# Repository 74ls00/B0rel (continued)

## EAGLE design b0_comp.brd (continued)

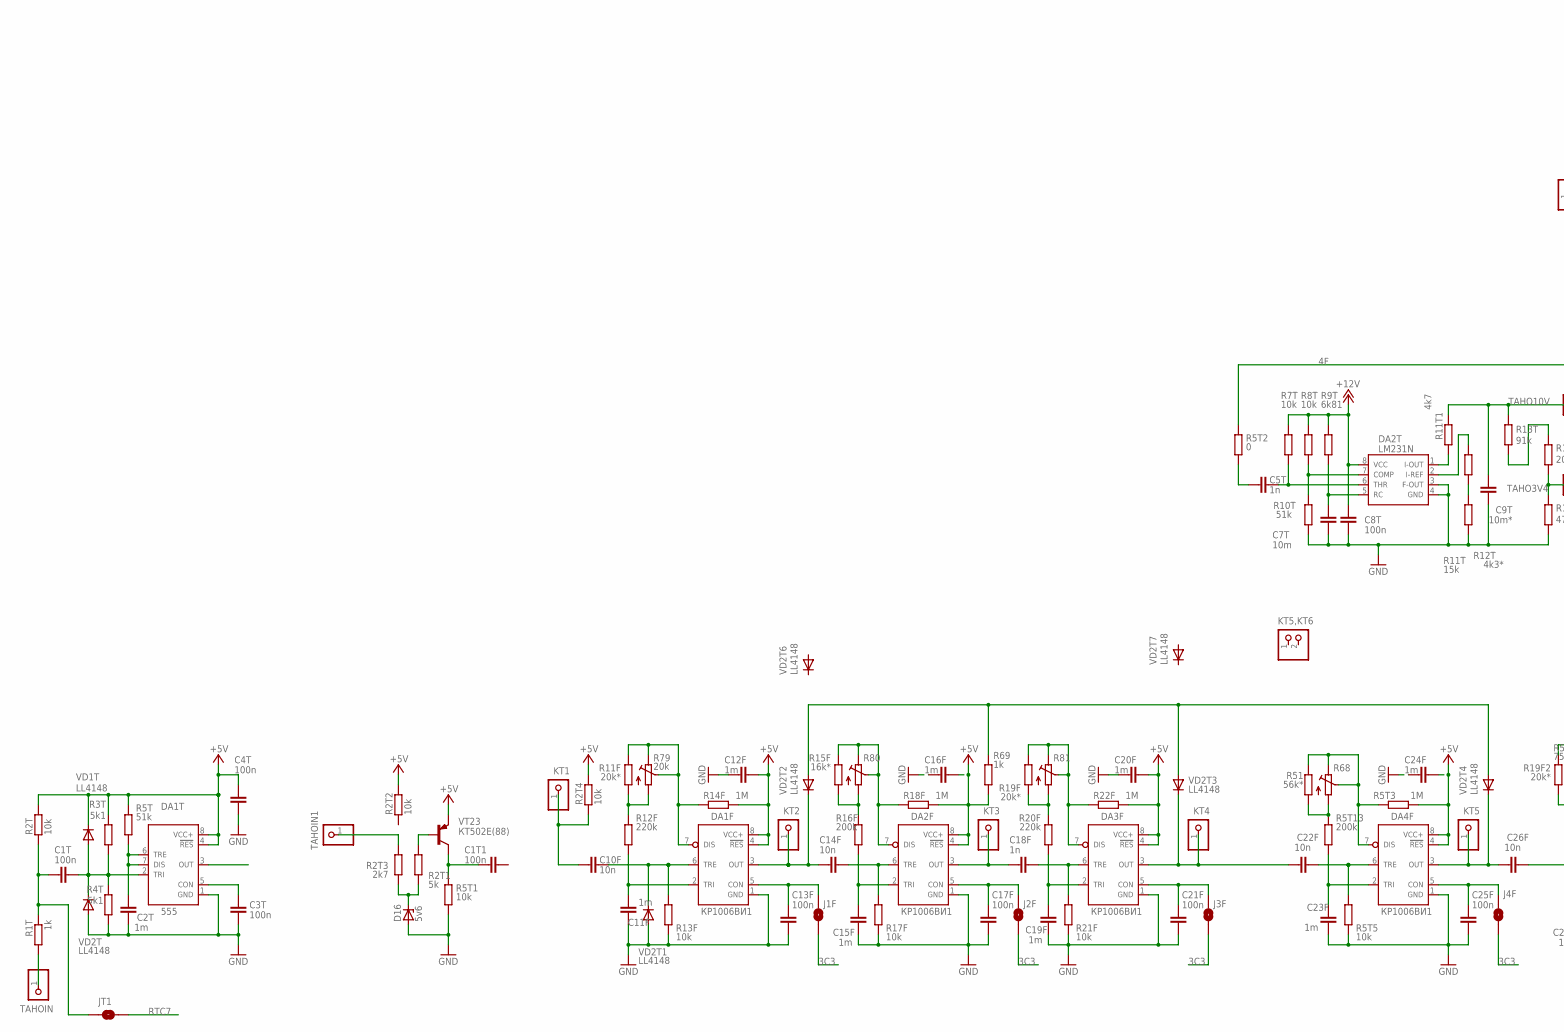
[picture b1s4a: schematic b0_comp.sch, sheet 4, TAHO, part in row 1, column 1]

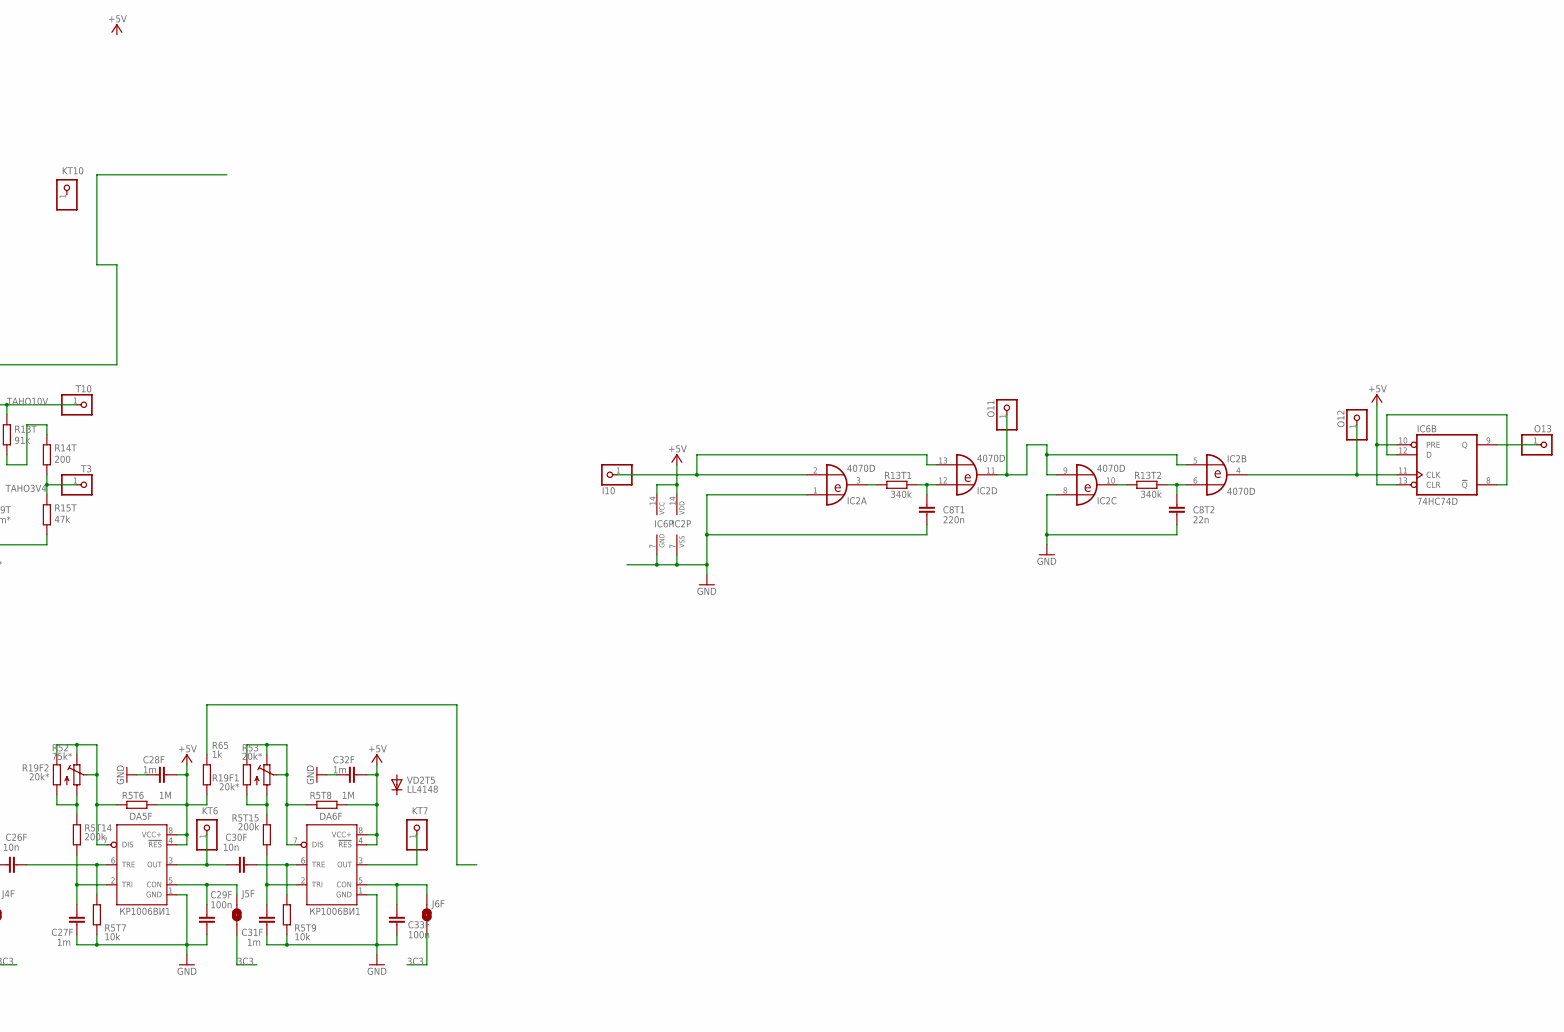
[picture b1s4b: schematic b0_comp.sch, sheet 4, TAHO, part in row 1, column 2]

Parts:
C1T, C1T1, C3T, C4T, C8T, C13F, C17F, C21F, C25F, C29F, C33F: 100n; C0805
C2T, C12F, C16F, C20F, C24F, C28F, C32F: 1m; C0805
C5T, C18F: 1n; C0805
C7T: 10m; C3225
C8T1: 220n; C0805
C8T2: 22n; C0805
C9T: 10m*; C3225
C10F, C14F, C22F, C26F, C30F: 10n; C0805
C11F, C15F, C19F, C23F, C27F, C31F: 1m; C90-065X115H
D16: 5v6; SOD80C
DA1F, DA2F, DA3F, DA4F, DA5F, DA6F: КР1006ВИ1; DIL8
DA1T: 555; DIL-08
DA2T: LM231N; DIL08
I10: PINHD-1X1; 1X01
IC2: 4070D; SO14
IC6: 74HC74D; SO14
J1F, J2F, J3F, J4F, J5F, J6F: SJ
JT1: SJ
KT1, KT2, KT3, KT4, KT5, KT6, KT7, KT10: PINHD-1X1; 1X01
KT5,KT6: PINHD-1X2/2; 1X02
O11, O12, O13: PINHD-1X1; 1X01
R1T, R65, R69: 1k; R0805
R2T, R2T2, R2T4, R5T1, R5T5, R5T7, R5T9, R7T, R8T, R13F, R17F, R21F: 10k; R0805
R2T1: 5k; R0805
R2T3: 2k7; R0805
R3T, R4T: 5k1; R0805
R5T, R10T: 51k; R0805
R5T2: 0; R0805
R5T3, R5T6, R5T8, R14F, R18F, R22F: 1M; R0805
R5T13, R5T14, R5T15, R16F: 200k; R0805
R9T: 6k81; R0805
R11F, R19F, R19F2: 20k*; 0207/10
R11T: 15k; R0805
R11T1: 4k7; R0805
R12F, R20F: 220k; R0805
R12T: 4k3*; R0805
R13T: 91k; R0805
R13T1, R13T2: 340k; R0805
R14T: 200; R0805
R15F: 16k*; 0207/10
R15T: 47k; R0805
R19F1: 20k*; 0207/11
R51: 56k*; 0207/10
R52: 75k*; RTRIM3314GJ
R53: 20k*; RTRIM3314G
R68, R80, R81: R-TRIMM3314GJ; RTRIM3314GJ
R79: 20k; RTRIM3314GJ
T3, T10: PINHD-1X1; 1X01
TAHOIN, TAHOIN1: PINHD-1X1; 1X01
VD1T, VD2T, VD2T1, VD2T2, VD2T3, VD2T4, VD2T5, VD2T6, VD2T7: LL4148; SOD80C
VT23: КТ502Е(88); TO92

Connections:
2F: R69.1, VD2T2.A, VD2T3.A, VD2T4.A
3C3: J1F.2, J2F.2, J3F.2, J4F.2, J5F.2, J6F.2
4F: R5T2.2
+5V: C4T.1, C12F.1, C16F.1, C20F.1, C24F.2, C28F.1, C32F.1, DA1F.4 (!RES), DA1F.8 (VCC+), DA1T.4 (!RES), DA1T.8 (VCC+), DA2F.4 (!RES), DA2F.8 (VCC+), DA3F.4 (!RES), DA3F.8 (VCC+), DA4F.4 (!RES), DA4F.8 (VCC+), DA5F.4 (!RES), DA5F.8 (VCC+), DA6F.4 (!RES), DA6F.8 (VCC+), IC2.14 (VDD), IC6.10 (PRE), IC6.13 (CLR), IC6.14 (VCC), R2T.2, R2T2.2, R2T4.2, R3T.2, R5T.2, R5T3.2, R5T6.2, R5T8.1, R14F.2, R18F.2, R22F.2, R65.2, R69.2, VD1T.C, VT23.3 (E); also elsewhere on the board
+12V: C8T.1, DA2T.8 (VCC), R7T.2, R8T.2, R9T.2; also elsewhere on the board
GND: C2T.2, C3T.2, C4T.2, C7T.2, C8T.2, C8T1.2, C8T2.2, C9T.2, C11F.1, C12F.2, C13F.2, C15F.2, C16F.2, C17F.2, C19F.2, C20F.2, C21F.2, C23F.2, C24F.1, C25F.2, C27F.2, C28F.2, C29F.2, C31F.2, C32F.2, C33F.2, D16.A, DA1F.1 (GND), DA1T.1 (GND), DA2F.1 (GND), DA2T.3 (F-OUT), DA2T.4 (GND), DA3F.1 (GND), DA4F.1 (GND), DA5F.1 (GND), DA6F.1 (GND), IC2.1 (I0), IC2.7 (VSS), IC2.8 (I0), IC6.7 (GND), R4T.1, R5T1.1, R5T5.1, R5T7.1, R5T9.1, R10T.1, R12T.1, R13F.1, R15T.1, R17F.1, R21F.1, VD2T.A, VD2T1.A; also elsewhere on the board
unnamed: C1T.1, JT1.1, R1T.1, R2T.1
unnamed: C25F.1, DA4F.5 (CON), J4F.1
unnamed: C3T.1, DA1T.5 (CON)
unnamed: D16.C, R2T1.1, R2T3.2
unnamed: C2T.1, DA1T.6 (TRE), DA1T.7 (DIS), R5T.1
unnamed: C23F.1, DA4F.2 (TRI), R5T13.1
unnamed: C1T1.1, R5T1.2, VT23.1 (C)
unnamed: R2T1.2, VT23.2 (B)
unnamed: R2T3.1, TAHOIN1.1
unnamed: C11F.2, DA1F.2 (TRI), R12F.1
unnamed: R1T.2, TAHOIN.1
unnamed: C1T.2, DA1T.2 (TRI), R3T.1, R4T.2, VD1T.A, VD2T.C
unnamed: I10.1, IC2.2 (I1), IC2.13 (I1)
unnamed: C7T.1, DA2T.5 (RC), R9T.1
unnamed: DA2T.7 (COMP), R8T.1, R10T.2
unnamed: DA2T.2 (I-REF), R11T.2
unnamed: R13T.2, R14T.2
unnamed: C5T.2, DA2T.6 (THR), R7T.1
unnamed: DA1F.7 (DIS), R11F.2, R14F.1, R79.1 (E), R79.1A (E), R79.2 (S)
unnamed: C10F.2, DA1F.6 (TRE), R13F.2, VD2T1.C
unnamed: C17F.1, DA2F.5 (CON), J2F.1
unnamed: R11F.1, R12F.2, R79.3 (A), R79.3A (A)
unnamed: C15F.1, DA2F.2 (TRI), R16F.1
unnamed: R11T.1, R12T.2
unnamed: DA2F.7 (DIS), R15F.2, R18F.1, R80.1 (E), R80.1A (E), R80.2 (S)
unnamed: C13F.1, DA1F.5 (CON), J1F.1
unnamed: C21F.1, DA3F.5 (CON), J3F.1
unnamed: R15F.1, R16F.2, R80.3 (A), R80.3A (A)
unnamed: C19F.1, DA3F.2 (TRI), R20F.1
unnamed: DA3F.7 (DIS), R19F.2, R22F.1, R81.1 (E), R81.1A (E), R81.2 (S)
unnamed: C18F.2, DA3F.6 (TRE), R21F.2
unnamed: C14F.2, DA2F.6 (TRE), R17F.2
unnamed: R19F.1, R20F.2, R81.3 (A), R81.3A (A)
unnamed: C5T.1, R5T2.1
unnamed: C10F.1, KT1.1, R2T4.1
unnamed: C22F.1, DA3F.3 (OUT), KT4.1, VD2T3.C
unnamed: C18F.1, DA2F.3 (OUT), KT3.1
unnamed: C29F.1, DA5F.5 (CON), J5F.1
unnamed: C14F.1, DA1F.3 (OUT), KT2.1, VD2T2.C
unnamed: C33F.1, DA6F.5 (CON), J6F.1
unnamed: DA6F.3 (OUT), KT7.1
unnamed: IC2.4 (O), IC6.11 (CLK), O12.1
unnamed: IC2.3 (O), R13T1.2
unnamed: C8T1.1, IC2.12 (I0), R13T1.1
unnamed: IC6.8 (!Q), IC6.12 (D)
unnamed: IC2.10 (O), R13T2.2
unnamed: DA2T.1 (I-OUT), R11T1.1
unnamed: IC2.5 (I0), IC2.9 (I1), IC2.11 (O), O11.1
unnamed: C8T2.1, IC2.6 (I1), R13T2.1
unnamed: R5T13.2, R51.1, R68.3 (A), R68.3A (A)
unnamed: R5T14.2, R19F2.1, R52.3 (A), R52.3A (A)
unnamed: IC6.9 (Q), O13.1
unnamed: DA4F.7 (DIS), R5T3.1, R51.2, R68.1 (E), R68.1A (E), R68.2 (S)
unnamed: C26F.1, DA4F.3 (OUT), KT5.1, VD2T4.C
unnamed: R5T15.2, R19F1.1, R53.3 (A)
unnamed: C22F.2, DA4F.6 (TRE), R5T5.2
unnamed: C27F.1, DA5F.2 (TRI), R5T14.1
unnamed: DA5F.7 (DIS), R5T6.1, R19F2.2, R52.1 (E), R52.1A (E), R52.2 (S)
unnamed: C26F.2, DA5F.6 (TRE), R5T7.2
unnamed: C31F.1, DA6F.2 (TRI), R5T15.1
unnamed: DA6F.7 (DIS), R5T8.2, R19F1.2, R53.1 (E), R53.2 (S)
unnamed: C30F.2, DA6F.6 (TRE), R5T9.2
unnamed: C30F.1, DA5F.3 (OUT), KT6.1
RTC7: JT1.2; also elsewhere on the board
TAHO3V4: R14T.1, R15T.2, T3.1
TAHO10V: C9T.1, R11T1.2, R13T.1, T10.1

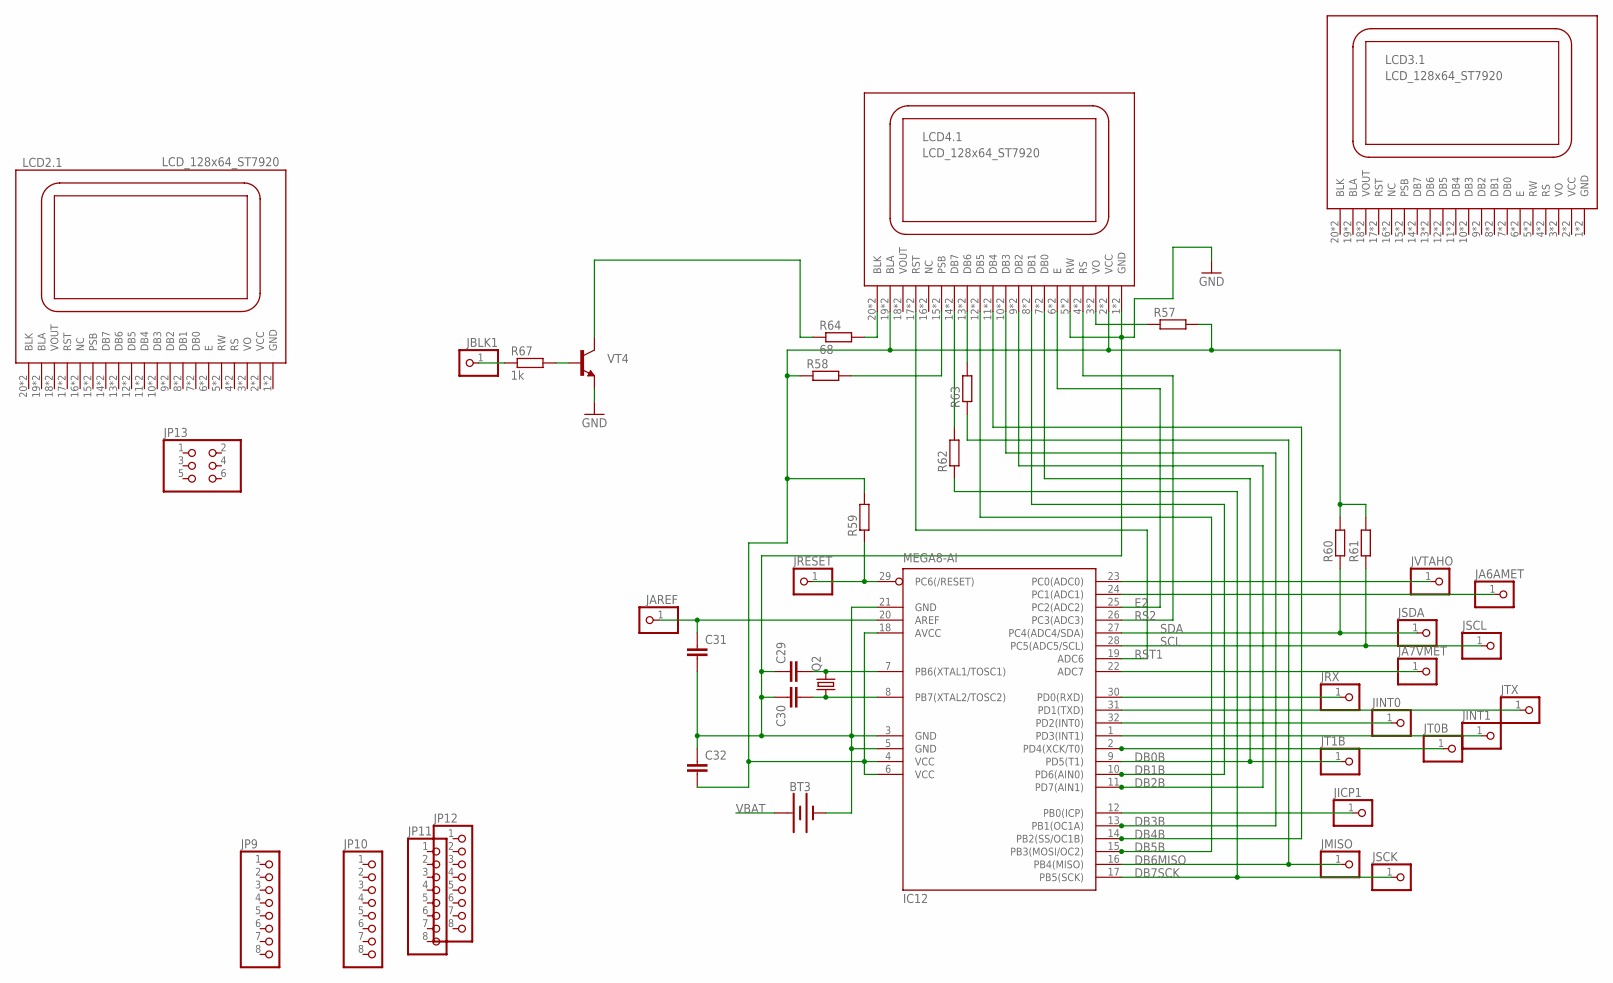
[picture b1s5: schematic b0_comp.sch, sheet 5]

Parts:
BT3: BATTERY-20MM_PTH; BATTCOM_20MM_PTH
C29, C30, C31, C32: C-EUC0805; C0805
IC12: MEGA8-AI; TQFP32-08
JA6AMET, JA7VMET: PINHD-1X1; 1X01
JAREF: PINHD-1X1; 1X01
JBLK1: PINHD-1X1; 1X01
JICP1: PINHD-1X1; 1X01
JINT0, JINT1: PINHD-1X1; 1X01
JMISO: PINHD-1X1; 1X01
JP9, JP10, JP11, JP12: PINHD-1X8; 1X08
JP13: PINHD-2X3/90; 2X03/90
JRESET: PINHD-1X1; 1X01
JRX: PINHD-1X1; 1X01
JSCK: PINHD-1X1; 1X01
JSCL: PINHD-1X1; 1X01
JSDA: PINHD-1X1; 1X01
JT0B, JT1B: PINHD-1X1; 1X01
JTX: PINHD-1X1; 1X01
JVTAHO: PINHD-1X1; 1X01
LCD2, LCD3, LCD4: LCD_128x64_ST7920; 12864B
Q2: CRYSTALHC49S; HC49/S
R57, R58, R59, R60, R61: R-EU_R0805; R0805
R62, R63: R-EU_R0603; R0603
R64: 68; R0805
R67: 1k; R0805
VT4: BJT_NPN_SOT23_BCE; SOT23

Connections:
DB0B: IC12.9 (PD5(T1)), JT1B.1, LCD4.7 (DB0), LCD4.7@ (DB0)
DB1B: IC12.10 (PD6(AIN0)), LCD4.8 (DB1), LCD4.8@ (DB1)
DB2B: IC12.11 (PD7(AIN1)), LCD4.9 (DB2), LCD4.9@ (DB2)
DB3B: IC12.13 (PB1(OC1A)), LCD4.10 (DB3), LCD4.10@ (DB3)
DB4B: IC12.14 (PB2(SS/OC1B)), LCD4.11 (DB4), LCD4.11@ (DB4)
DB5B: IC12.15 (PB3(MOSI/OC2)), LCD4.12 (DB5), LCD4.12@ (DB5)
DB6MISO: IC12.16 (PB4(MISO)), JMISO.1, R63.1
DB7SCK: IC12.17 (PB5(SCK)), JSCK.1, R62.1
E2: IC12.25 (PC2(ADC2)), LCD4.6 (E), LCD4.6@ (E)
GND: BT3.2 (-), C29.1, C30.1, C31.2, C32.1, IC12.3 (GND), IC12.5 (GND), IC12.21 (GND), LCD4.1 (GND), LCD4.1@ (GND), LCD4.5 (RW), LCD4.5@ (RW), VT4.2 (E); also elsewhere on the board
unnamed: R67.2, VT4.1 (B)
unnamed: R64.1, VT4.3 (C)
unnamed: JBLK1.1, R67.1
unnamed: LCD4.3 (VO), LCD4.3@ (VO), R57.1
unnamed: IC12.32 (PD2(INT0)), JINT0.1
unnamed: IC12.12 (PB0(ICP)), JICP1.1
unnamed: LCD4.15 (PSB), LCD4.15@ (PSB), R58.2
unnamed: IC12.2 (PD4(XCK/T0)), JT0B.1
unnamed: IC12.30 (PD0(RXD)), JRX.1
unnamed: IC12.22 (ADC7), JA7VMET.1
unnamed: IC12.24 (PC1(ADC1)), JA6AMET.1
unnamed: IC12.29 (PC6(/RESET)), JRESET.1, R59.1
unnamed: IC12.23 (PC0(ADC0)), JVTAHO.1
unnamed: LCD4.14 (DB7), LCD4.14@ (DB7), R62.2
unnamed: C29.2, IC12.7 (PB6(XTAL1/TOSC1)), Q2.2
unnamed: C30.2, IC12.8 (PB7(XTAL2/TOSC2)), Q2.1
unnamed: LCD4.13 (DB6), LCD4.13@ (DB6), R63.2
unnamed: IC12.1 (PD3(INT1)), JINT1.1
unnamed: LCD4.20 (BLK), LCD4.20@ (BLK), R64.2
unnamed: IC12.31 (PD1(TXD)), JTX.1
unnamed: C31.1, IC12.20 (AREF), JAREF.1
RS2: IC12.26 (PC3(ADC3)), LCD4.4 (RS), LCD4.4@ (RS)
RST1: IC12.19 (ADC6), LCD4.17 (RST), LCD4.17@ (RST)
SCL: IC12.28 (PC5(ADC5/SCL)), JSCL.1, R61.1; also elsewhere on the board
SDA: IC12.27 (PC4(ADC4/SDA)), JSDA.1, R60.1; also elsewhere on the board
VBAT: BT3.1 (+); also elsewhere on the board
VCCV2: C32.2, IC12.4 (VCC), IC12.6 (VCC), IC12.18 (AVCC), LCD4.2 (VCC), LCD4.2@ (VCC), LCD4.19 (BLA), LCD4.19@ (BLA), R57.2, R58.1, R59.2, R60.2, R61.2

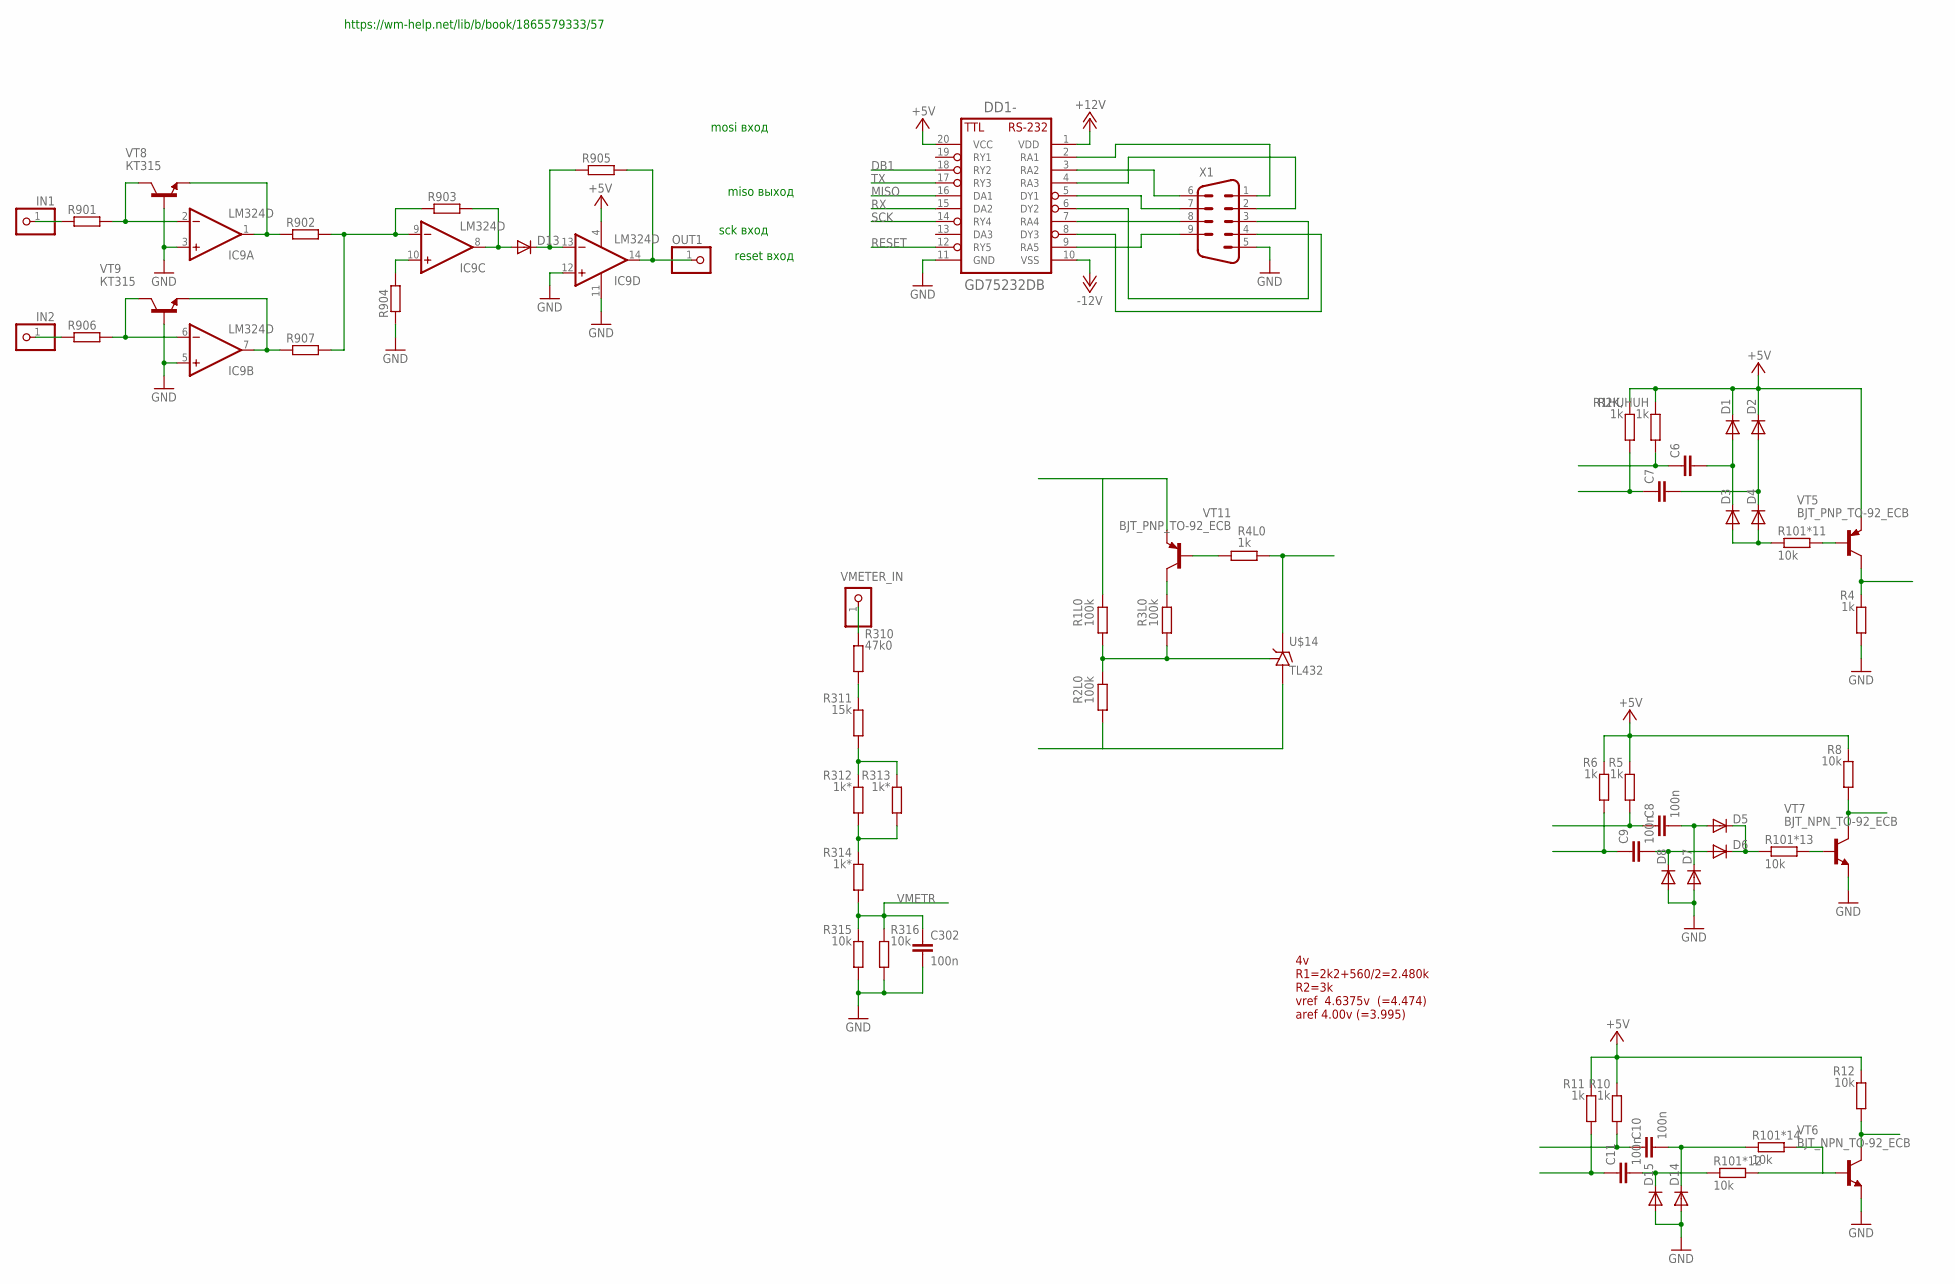
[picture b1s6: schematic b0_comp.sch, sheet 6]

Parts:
C6, C7: C-EUC0805; C0805
C8, C9, C10, C11, C302: 100n; C0805
D1, D2, D3, D4, D5, D6, D7, D8, D13, D14, D15: DIODE-SOD80C; SOD80C
DD1-: GD75232DB; SSOP20D8
IC9: LM324D; SO14
IN1, IN2: PINHD-1X1; 1X01
OUT1: PINHD-1X1; 1X01
R1HUHUH, R2K,, R4, R4L0, R5, R6, R10, R11: 1k; R0805
R1L0, R2L0, R3L0: 100k; R0805
R8, R12, R101*11, R101*12, R101*13, R101*14, R315, R316: 10k; R0805
R310: 47k0; R0805
R311: 15k; R0805
R312, R313, R314: 1k*; R0805
R901, R902, R903, R904, R905, R906, R907: R-EU_R0805; R0805
U$14: TL432; SOT-23
VMETER_IN: PINHD-1X1; 1X01
VT5, VT11: BJT_PNP_TO-92_ECB; TO92
VT6, VT7: BJT_NPN_TO-92_ECB; TO92
VT8, VT9: КТ315; TO92
X1: M09-182; 182-009-MALE

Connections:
+5V: D1.C, D2.C, DD1-.20 (VCC), IC9.4 (V+), R1HUHUH.2, R2K,.2, R5.2, R6.2, R8.2, R10.2, R11.2, R12.2, VT5.1 (E); also elsewhere on the board
+12V: DD1-.1 (VDD); also elsewhere on the board
-12V: DD1-.10 (VSS)
DB1: DD1-.18 (RY2); also elsewhere on the board
GND: C302.2, D7.A, D8.A, D14.A, D15.A, DD1-.11 (GND), IC9.3 (+IN), IC9.5 (+IN), IC9.11 (V-), IC9.12 (+IN), R4.1, R315.1, R316.1, R904.1, VT6.1 (E), VT7.1 (E), VT8.3 (B), VT9.3 (B), X1.5; also elsewhere on the board
MISO: DD1-.16 (DA1); also elsewhere on the board
unnamed: R312.1, R313.1, R314.2
unnamed: D3.A, D4.A, R101*11.1
unnamed: C6.2, D1.A, D3.C
unnamed: C7.2, D2.A, D4.C
unnamed: R101*13.2, VT7.3 (B)
unnamed: R101*11.2, VT5.3 (B)
unnamed: C6.1, R1HUHUH.1
unnamed: C7.1, R2K,.1
unnamed: C8.2, D5.A, D7.C
unnamed: R4.2, VT5.2 (C)
unnamed: C9.2, D6.A, D8.C
unnamed: C8.1, R5.1
unnamed: C9.1, R6.1
unnamed: R8.1, VT7.2 (C)
unnamed: D5.C, D6.C, R101*13.1
unnamed: C10.1, R10.1
unnamed: C11.1, R11.1
unnamed: C10.2, D14.C, R101*14.1
unnamed: R101*12.2, R101*14.2, VT6.3 (B)
unnamed: DD1-.9 (RA5), X1.9
unnamed: R12.1, VT6.2 (C)
unnamed: C11.2, D15.C, R101*12.1
unnamed: DD1-.8 (DY3), X1.4
unnamed: DD1-.7 (RA4), X1.8
unnamed: R310.1, R311.2
unnamed: DD1-.6 (DY2), X1.3
unnamed: DD1-.5 (DY1), X1.7
unnamed: DD1-.4 (RA3), X1.2
unnamed: DD1-.3 (RA2), X1.6
unnamed: DD1-.2 (RA1), X1.1
unnamed: R311.1, R312.2, R313.2
unnamed: R310.2, VMETER_IN.1
unnamed: IC9.6 (-IN), R906.2, VT9.2 (C)
unnamed: R3L0.2, VT11.2 (C)
unnamed: R4L0.1, VT11.3 (B)
unnamed: R4L0.2, U$14.2 (C)
unnamed: R1L0.2, VT11.1 (E)
unnamed: R2L0.1, U$14.3 (A)
unnamed: R1L0.1, R2L0.2, R3L0.1, U$14.1 (R)
unnamed: IC9.2 (-IN), R901.2, VT8.2 (C)
unnamed: IC9.1 (OUT), R902.1, VT8.1 (E)
unnamed: IC9.7 (OUT), R907.1, VT9.1 (E)
unnamed: IC9.9 (-IN), R902.2, R903.1, R907.2
unnamed: IC9.10 (+IN), R904.2
unnamed: D13.A, IC9.8 (OUT), R903.2
unnamed: D13.C, IC9.13 (-IN), R905.1
unnamed: IC9.14 (OUT), OUT1.1, R905.2
unnamed: IN1.1, R901.1
unnamed: IN2.1, R906.1
RESET: DD1-.12 (RY5); also elsewhere on the board
RX: DD1-.15 (DA2)
SCK: DD1-.14 (RY4); also elsewhere on the board
TX: DD1-.17 (RY3)
VMETR: C302.1, R314.1, R315.2, R316.2; also elsewhere on the board

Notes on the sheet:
https://wm-help.net/lib/b/book/1865579333/57
mosi вход
sck вход
miso выход
reset вход
4v R1=2k2+560/2=2.480k R2=3k vref 4.6375v (=4.474) aref 4.00v (=3.995)

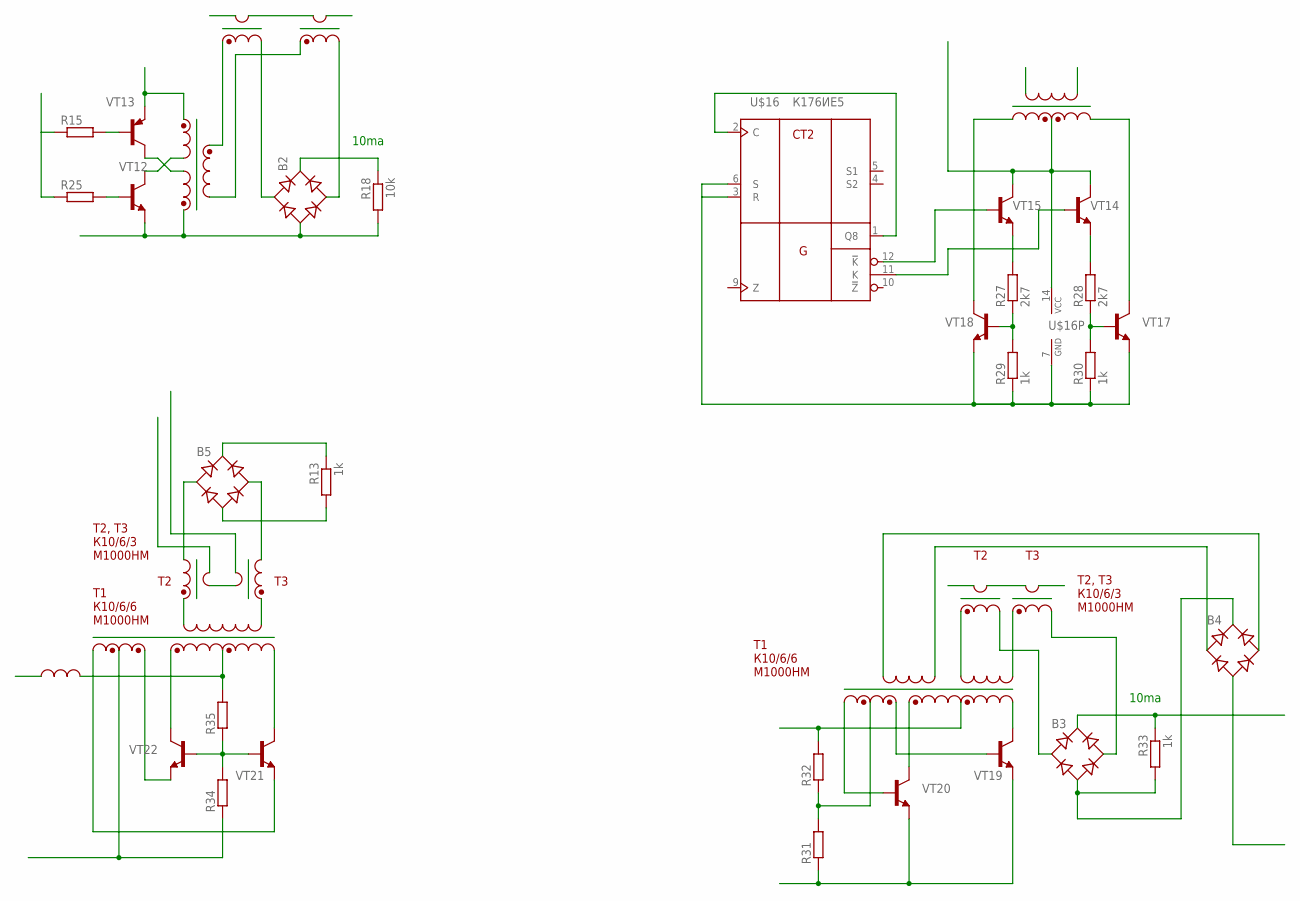
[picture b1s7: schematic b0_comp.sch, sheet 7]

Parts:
B2, B3, B4, B5: DBDB105G; DB
R13, R33: 1k; 0411/12
R15, R25, R31, R32, R34, R35: R-EU_0411/12; 0411/12
R18: 10k; 0411/12
R27, R28: 2k7; R0805
R29, R30: 1k; R0805
U$16: К176ИЕ5; DIL14
VT12, VT19, VT20, VT21, VT22: BJT_NPN_TO-92_CBE; TO92
VT13: BJT_PNP_SOT23_BCE; SOT23
VT14, VT15, VT17, VT18: BJT_NPN_TO-92_ECB; TO92

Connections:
unnamed: B5.-, R13.2
unnamed: B5.+, R13.1
unnamed: R15.2, VT13.1 (B)
unnamed: B2.-, R18.2, VT12.3 (E)
unnamed: B2.+, R18.1
unnamed: R25.2, VT12.2 (B)
unnamed: R15.1, R25.1
unnamed: U$16.1 (Q8), U$16.2 (C)
unnamed: U$16.12 (!K), VT15.3 (B)
unnamed: U$16.11 (K), VT14.3 (B)
unnamed: U$16.14 (VCC), VT14.2 (C), VT15.2 (C)
unnamed: R28.1, R30.2, VT17.3 (B)
unnamed: R28.2, VT14.1 (E)
unnamed: R27.2, VT15.1 (E)
unnamed: R27.1, R29.2, VT18.3 (B)
unnamed: R29.1, R30.1, U$16.3 (R), U$16.6 (S), U$16.7 (GND), VT17.1 (E), VT18.1 (E)
unnamed: R31.1, VT19.3 (E), VT20.3 (E)
unnamed: B3.-, B4.+, R33.2
unnamed: R31.2, R32.1
unnamed: B3.+, R33.1
unnamed: R34.2, R35.1, VT21.2 (B), VT22.2 (B)

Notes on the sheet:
10ma
T1 К10/6/6 М1000НМ
T2, Т3 К10/6/3 М1000НМ

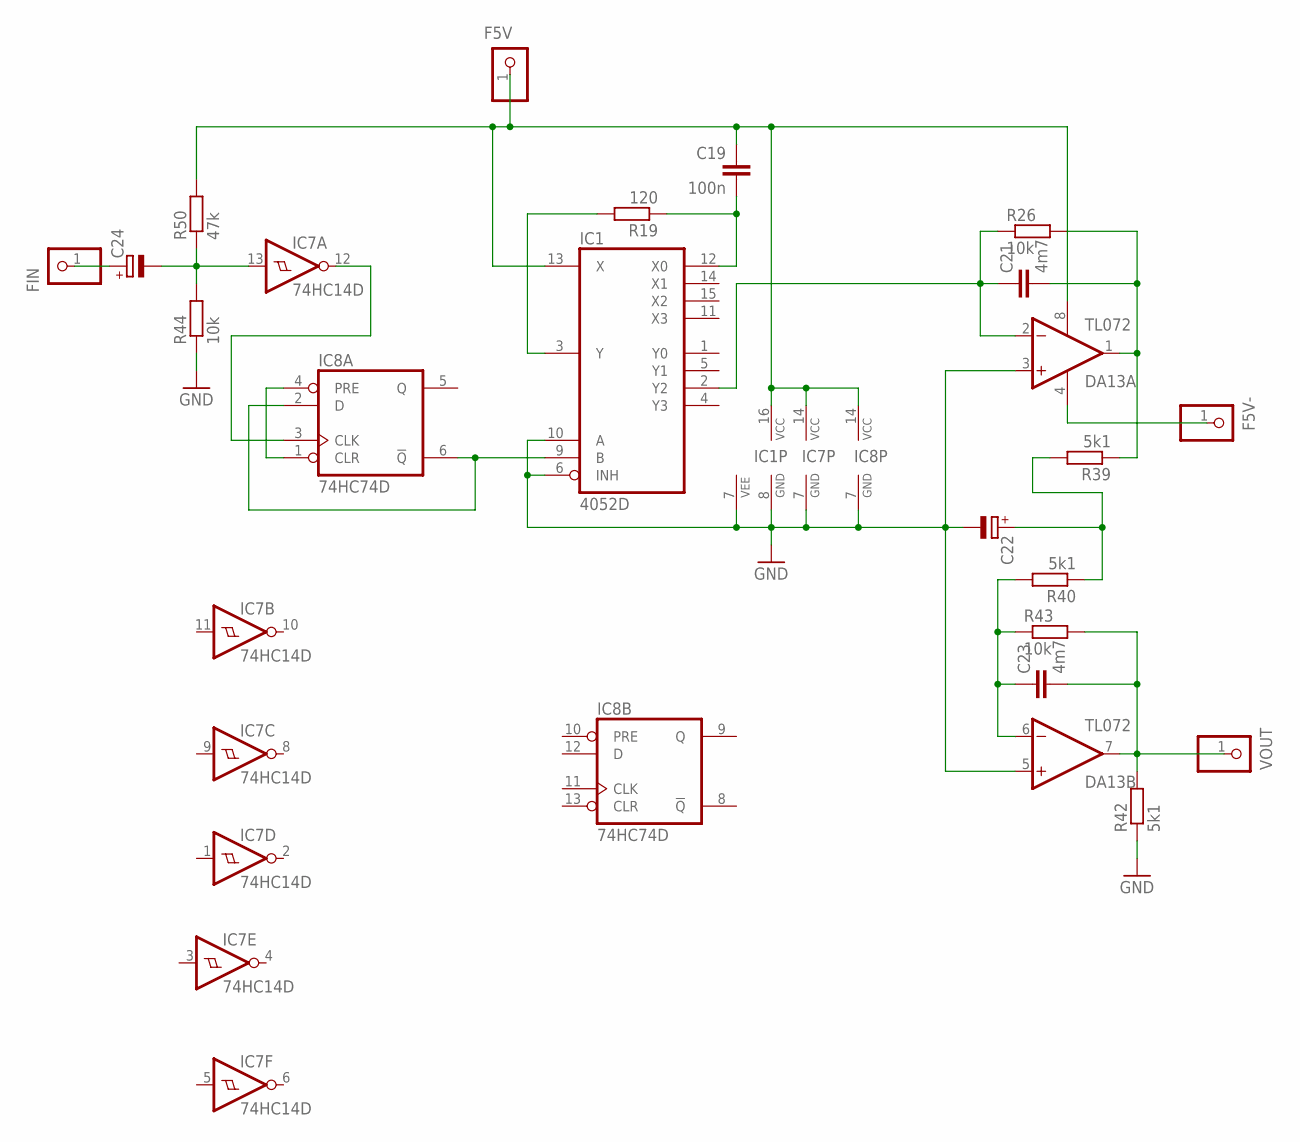
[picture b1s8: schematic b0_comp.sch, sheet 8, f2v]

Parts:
C19: 100n; C0805
C21, C23: 4m7; C1206
C22, C24: CPOL-EUE2.5-6; E2,5-6
DA13: TL072; SO08
F5V, F5V-: PINHD-1X1; 1X01
FIN: PINHD-1X1; 1X01
IC1: 4052D; SO16
IC7: 74HC14D; SO14
IC8: 74HC74D; SO14
R19: 120; R0805
R26, R43, R44: 10k; R0805
R39, R40, R42: 5k1; R0805
R50: 47k; R0805
VOUT: PINHD-1X1; 1X01

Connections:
GND: C22.-, DA13.3 (+IN), DA13.5 (+IN), IC1.6 (INH), IC1.7 (VEE), IC1.8 (GND), IC1.10 (A), IC7.7 (GND), IC8.7 (GND), R42.1, R44.1; also elsewhere on the board
unnamed: IC1.3 (Y), R19.2
unnamed: C21.1, DA13.2 (-IN), IC1.2 (Y2), R26.1
unnamed: C19.2, IC1.12 (X0), R19.1
unnamed: C19.1, DA13.8 (V+), F5V.1, IC1.13 (X), IC1.16 (VCC), IC7.14 (VCC), IC8.14 (VCC), R50.2
unnamed: C24.+, FIN.1
unnamed: IC7.12 (O), IC8.3 (CLK)
unnamed: C21.2, DA13.1 (OUT), R26.2, R39.1
unnamed: IC8.1 (CLR), IC8.4 (PRE)
unnamed: C22.+, R39.2, R40.1
unnamed: C23.1, DA13.6 (-IN), R40.2, R43.1
unnamed: C23.2, DA13.7 (OUT), R42.2, R43.2, VOUT.1
unnamed: IC1.9 (B), IC8.2 (D), IC8.6 (!Q)
unnamed: DA13.4 (V-), F5V-.1
unnamed: C24.-, IC7.13 (I), R44.2, R50.1

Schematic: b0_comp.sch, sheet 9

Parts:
+5V2, +15VP: PINHD-1X1; 1X01
-5V2, -15VP: PINHD-1X1; 1X01
C2M, C4M, C40, C41, C42: 100n; C0805
C3M: 4p7; C0805
C5M, C7M: 1m; C0805
C6M, C39: 100p; C0805
C33, C34: C-EUC0805; C0805
D17, D18: SCHOTTKY-DIODESMD; SMB
DA1M: LT1945EMS; MSOP10
DA1M1: DIL10
DA20: TL432; SOT-23
DA100: КМ525ПС3Б; DIL14
DA148: КP1211ЕУ1; DIL8
GNDP: PINHD-1X1; 1X01
I+5V: PINHD-1X1; 1X01
INX: PINHD-1X1; 1X01
INY: PINHD-1X1; 1X01
JP14, JP15, JP16: PINHD-1X2/90; 1X02/90
KOUT: PINHD-1X1; 1X01
L1M: L0207/7; 0207/7
L2M: murata LQH3C100; 0207/7
O+15V: PINHD-1X1; 1X01
O-15V1: PINHD-1X1; 1X01
OFB+: PINHD-1X1; 1X01
OFB-: PINHD-1X1; 1X01
OGND, OGND2: PINHD-1X1; 1X01
OK2: LTV816; DIL04
R66: 120k; R0805
R70: 11k*; R0805
R71: 47k; R0805
R72: 4k3*; R0805
R73, R76: 3k3; R0805
R74, R75, R78: R-EU_R0805; R0805
R77: R-EU_0207/11; 0207/11
R82: R-EU_0207/7; 0207/7
Rнагр.: 80ом для 8в.вх.; R0805
U$1: 78L05F; SOT89
U$30, U$32, U$33, U$34, U$35: T_PIN_NONAME; PIN1X1N
VD1M, VD2M, VD3M: SS34china; SMB
VT10: BJT_PNP_SOT23_BCE; SOT23
VT24, VT25: MOSFET-N_DPACK; DPACK

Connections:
+5V: C40.1, DA148.8 (VCC), JP15.2, R76.1, VT10.2 (E); also elsewhere on the board
+15V: +15VP.1, C34.1, DA100.14 (+U)
-15V: -15VP.1, C33.1, DA100.8 (-U)
GND: C33.2, C34.2, C39.2, C40.2, DA100.2 (X2), DA100.7 (Y2), DA100.10 (Z2), DA148.1 (FC), DA148.2 (FV), DA148.3 (IN), DA148.5 (GND), GNDP.1, JP15.1, OK2.3 (EMIT), VT24.S, VT25.S; also elsewhere on the board
LTFB2: C3M.2, DA1M.5 (FB2), DA1M1.5, OFB+.1, R71.2, R72.2
LTNFB1: C6M.1, DA1M.1 (NFB1), DA1M1.1, OFB-.1, R66.1, R70.2
LTSW1: C4M.2, DA1M.10 (SW1), DA1M1.10, L2M.2
LTSW2: DA1M.6 (SW2), DA1M1.6, L1M.2, VD1M.A
LTV+: C2M.1, DA1M.2 (!SHDN1), DA1M.4 (!SHDN2), DA1M.8 (VIN), DA1M1.2, DA1M1.4, DA1M1.8, I+5V.1, L1M.1, L2M.1
unnamed: DA100.1 (X1), INX.1
unnamed: DA100.6 (Y1), INY.1
unnamed: DA100.11 (Z1), DA100.12 (OUT), KOUT.1
unnamed: C3M.1, C7M.1, O+15V.1, R71.1, VD1M.C
unnamed: OK2.1 (A), R74.2
unnamed: C5M.2, C6M.2, O-15V1.1, R66.2, VD3M.A
unnamed: C4M.1, VD2M.A, VD3M.C
unnamed: C39.1, DA148.7 (T), R73.2
unnamed: DA148.6 (OUT1), R77.2, U$32.1
unnamed: -5V2.1, C41.2, C42.2, OK2.2 (C), U$33.1
unnamed: DA148.4 (OUT2), R78.2, U$30.1
unnamed: +5V2.1, C41.1, C42.1, D17.C, D18.C, R74.1
unnamed: OK2.4 (COL), R75.1
unnamed: D17.A, U$34.1
unnamed: D18.A, U$35.1
unnamed: R73.1, R76.2, VT10.3 (C)
unnamed: R75.2, VT10.1 (B)
unnamed: R78.1, VT25.G
unnamed: R77.1, VT24.G
OGND: C2M.2, C5M.1, C7M.2, DA1M.3 (GND), DA1M.7 (PGND), DA1M.9 (PGND), DA1M1.3, DA1M1.7, DA1M1.9, OGND.1, OGND2.1, R70.1, R72.1, VD2M.C

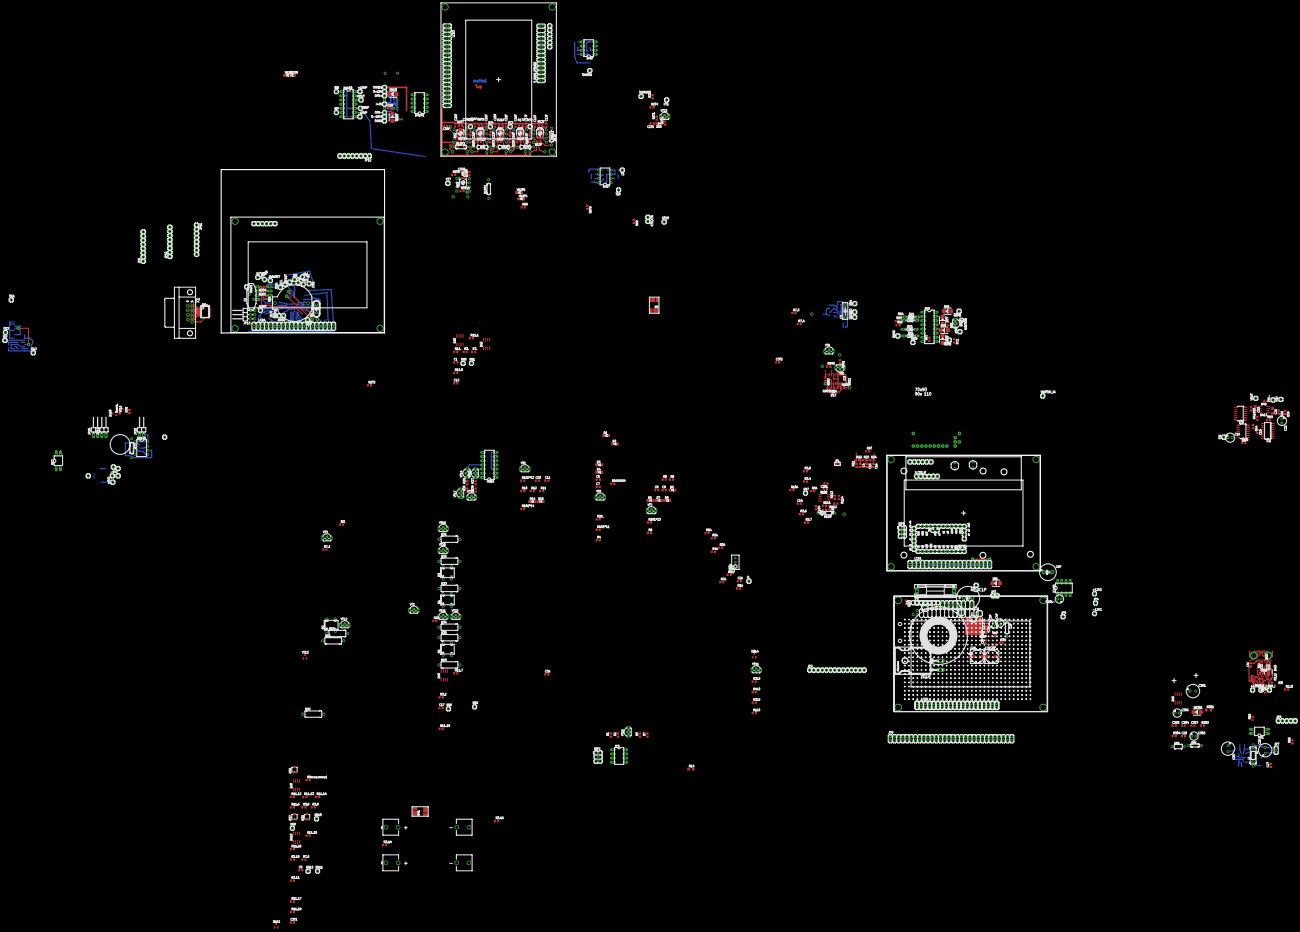
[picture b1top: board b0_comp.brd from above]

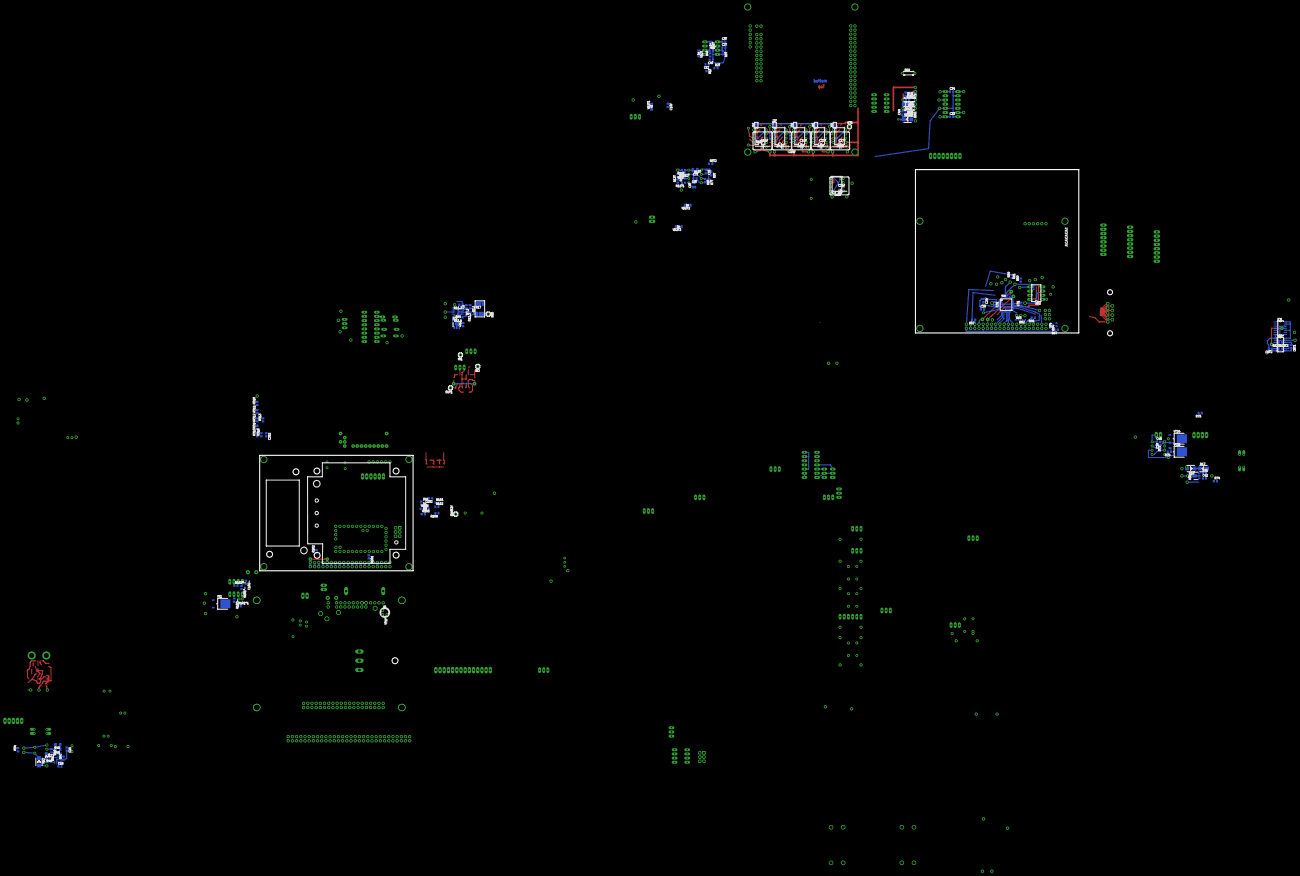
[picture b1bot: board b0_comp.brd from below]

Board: 2 copper layers, 619 parts (151 on the bottom side), 392 nets.

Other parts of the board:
U$2: 18650
U$3: DIMEN10X10

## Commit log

2020-05-13 board frame
2020-10-21 vmetr
2020-10-23 vm amp
2020-10-29 jfetstab
2020-11-27 -dc l
2021-02-16 bad date
2021-05-12 4052 f2v
2021-05-18 pro mc
2021-05-21 r400k
2021-05-22 sch err
2021-12-12 fix c
2022-01-14 2022
